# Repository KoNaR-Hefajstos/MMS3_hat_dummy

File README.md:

# MMS3 hat Dummy

## Sekcja 1: Dokumentacja Hat'a

### Krótki opis projektu
Hat Dummy to dystans mechaniczny. Tylko tyle

### Zgodność ze standardem ChainBus

* ❌ Używa złącza ChainBus, nie zmienia jego miejsca ani pinoutu. -> nie przesuwa addresów hat'a. Robi za głupi dystans mechaniczny
* ✅  Używa wyłącznie interfejsów I2C, SPI lub UART i nie inicjuje samodzielnie nowych transmisji (Nie jest master'em I2C albo SPI).
* ❌ Spełnia wymagania mechaniczne standardu (wymiary PCB, rozstaw otworów). -> Jest troche mniejszy
* ✅ Pobiera maksymalny prąd zgodny z ilością na jednego hat'a
* ✅ Obsługuje napięcie wejściowe BRD_VIN do wartości 48V.

### Komunikacja i adresowanie

Hat nie ma na sobie żadnych urządzeń

### Pinout złączy
Brak

### Konfiguracja układu (Zworki/Rezystory)
Brak

### Szczegółowy opis techniczny
Hat Dummy to dystans mechaniczny. Możesz go dać jeśli potrzebujesz mieć fizycznie więcej miejsca miedzy hat'ami. Nie zużywa adresu hat'a -> możesz go włożyć w dowolne miejsce między inne hat'y i elektrycznie ani programowo się nic nie zmieni

Bonusowo ma led'y które się świecą jak wybierzesz jakiegoś hat'a za nim. Elektrycznie nic nie zmienia

### Gotowe arkusze hierarchiczne
Brak

---

## Sekcja 2: Specyfikacja standardu ChainBus

### Architektura i łączenie modułów
Standard ChainBus umożliwia modułowe łączenie hatów. Na jednym MMS3 można zamontować pionowo **do 8 hat'ów**. Połączenie realizowane jest poprzez wpięcie złącza męskiego kolejnego hat'a w złącze żeńskie poprzedniego

### Komunikacja i sterowanie
Magistrala ChainBus jest w pełni cyfrowa. Płyta główna nie steruje bezpośrednio sygnałami ogólnego przeznaczenia (GPIO) na poszczególnych hat'ach. Wszelkie operacje (np. obsługa diod LED, odczyt krańcówek, generowanie sygnałów PWM) muszą być realizowane przez dedykowane układy scalone (np. ekspandery portów, sterowniki) komunikujące się przez interfejsy systemowe.

*Przykład:*
`MCU` $\rightarrow$ `Expander GPIO po I2C` $\rightarrow$ `Dioda LED`

Wybór aktywnego modułu realizowany jest przez układ przełącznika magistrali (bus switch) na płycie głównej. Dzięki temu linie I2C, SPI i UART są niezależne dla każdego hat'a (brak konfliktów adresów I2C między różnymi hatami).
* **Identyfikacja:** Każdy moduł powinien posiadać pamięć EEPROM na magistrali I2C w celu identyfikacji płyty przez system - układ M24C64-W skonfigurowany na adres `1010000` przy liniach adresowych A0, A1, A2 zwartych do masy.

### Zasilanie
Złącze ChainBus dostarcza następujące linie zasilania:

| Magistrala zasilania | Napięcie znamionowe | Maksymalny prąd (łączny dla 8 hatów) | Szacowany prąd na jeden hat |
| :------------------- | :-----------------: | :----------------------------------: | :-------------------------: |
| **5V**               |        5.0 V        |                1.0 A                 |           125 mA            |
| **12V stby**         |       12.0 V        |                0.5 A                 |            65 mA            |
| **BRD_VIN**          |   12.0 V – 48.0 V   |                1.5 A                 |           185 mA            |

*   Komponenty podłączone do linii `BRD_VIN` muszą być przystosowane do pracy z napięciem od 12V do **48 V**.
*   W przypadku zapotrzebowania na wyższą moc, dopuszczalne jest zastosowanie dodatkowego złącza zasilania XT60 (obciążalność do ok. 60 A).

### Wymagania mechaniczne i złącza
* **Wymiary PCB:** Niedozwolona jest zmiana obrysu płytki oraz położenia otworów montażowych, aby zachować kompatybilność mechaniczną.
* **Pozycjonowanie złączy ChainBus:** Położenie złącza standardu 2x16 SMD (raster 2.54 mm) musi być zgodne z szablonem. Złącze żeńskie montowane jest na stronie FRONT, natomiast złącze męskie na stronie BACK.
* **Interfejsy zewnętrzne:** Złącza wejścia/wyjścia (domyślnie standard JST-XH 2.5 mm o obciążalności do 3 A) oraz opcjonalne złącze XT60 powinny być umieszczone przy dolnej krawędzi płytki. Elementy regulacyjne i sygnalizacyjne (potencjometry, przełączniki, diody LED) należy lokalizować przy prawej krawędzi płytki.
* **Komponenty** Wszystkie komponenty powinny być na stronie front płytki żeby nie haczyły o elementy ze wcześniejszego hat'a

---

## Sekcja 3: Licencje

### Licencje projektu

*   **PCB:** CERN-OHL-P
*   **Software:** MIT License

[Template](https://github.com/KoNaR-Hefajstos/MMS3_hat_templates/) jest na licencji CC0 1.0 Universal. **Reszta projektu nie jest na tej licencji**

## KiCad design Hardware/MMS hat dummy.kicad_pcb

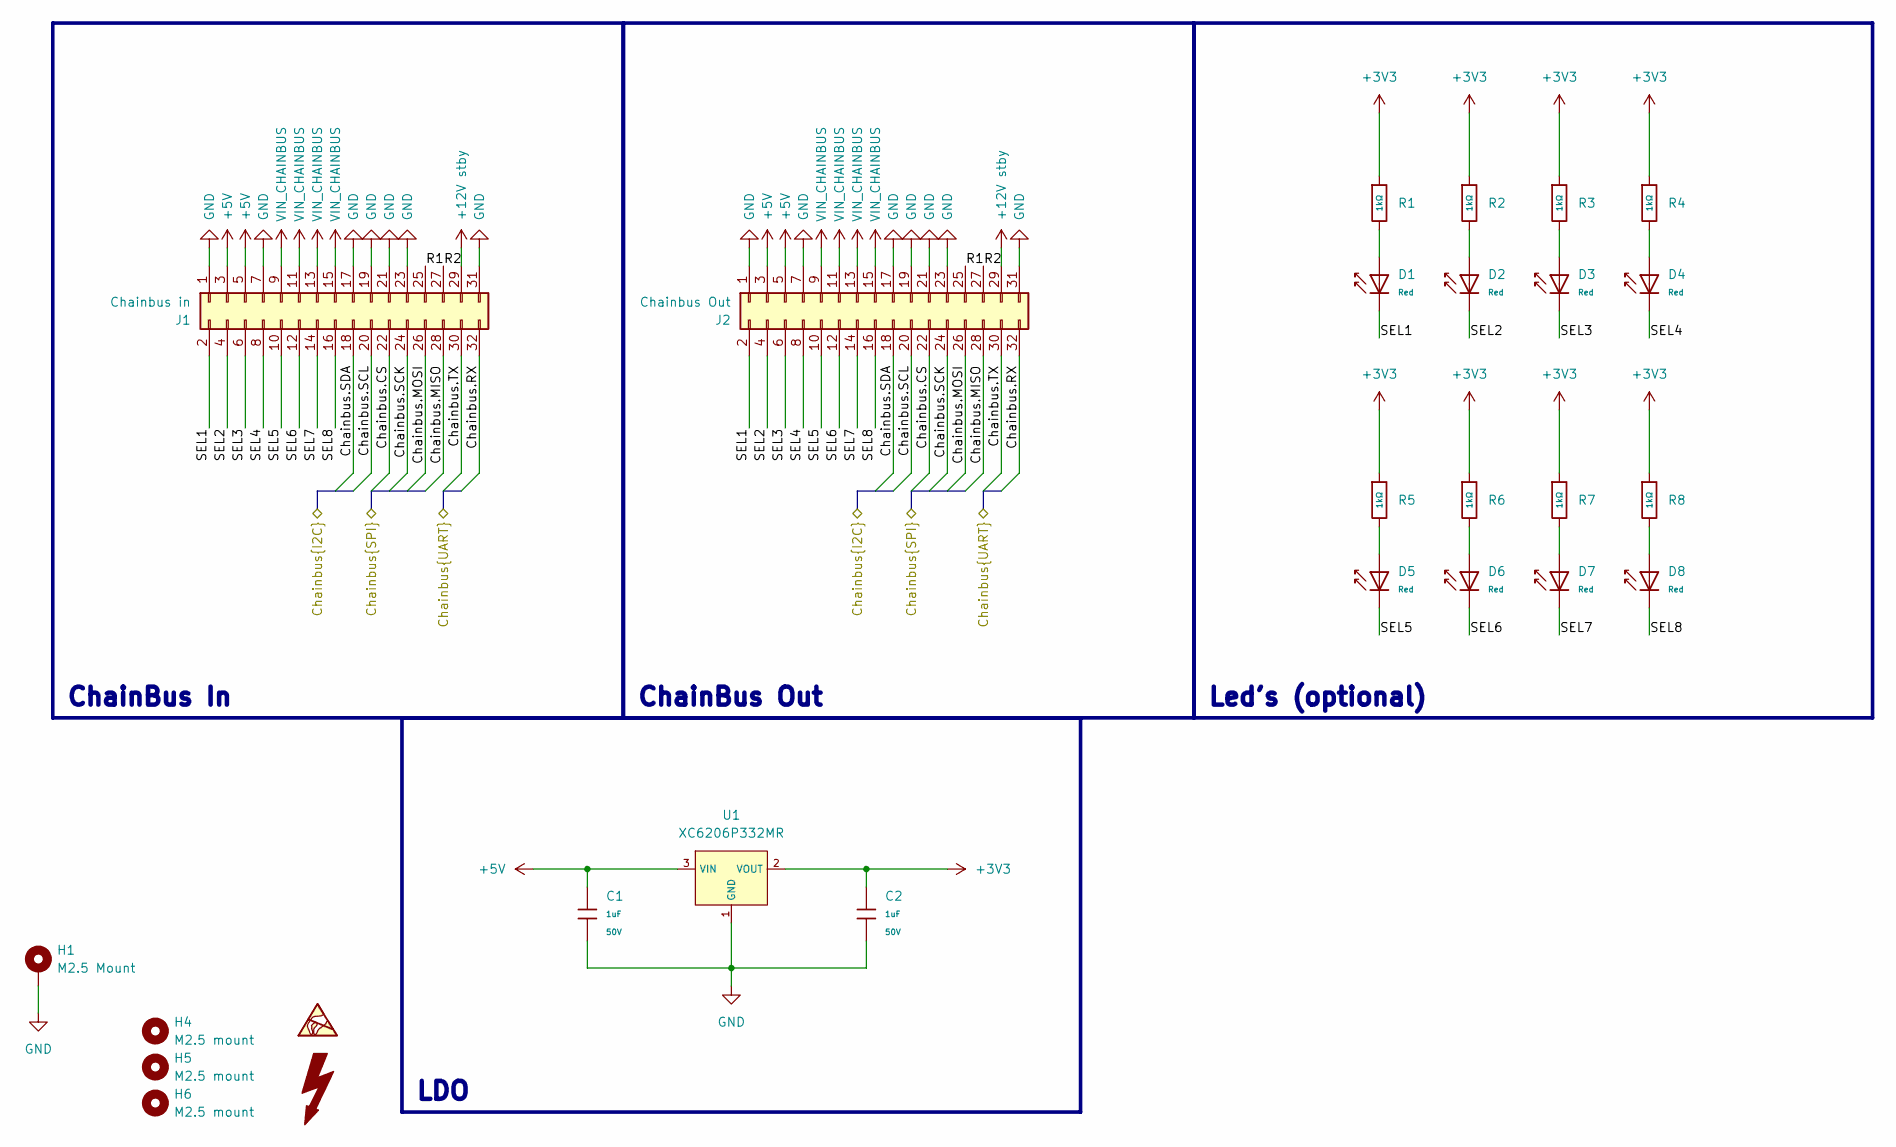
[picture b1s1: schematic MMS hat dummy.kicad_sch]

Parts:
C1, C2: 1uF; C_0603; Voltage Rated 50V; Tolerance ±10%; Part CL10A105KB8NNNC; LCSC C15849
D1, D2, D3, D4, D5, D6, D7, D8: Red; D_0603; Part KT-0603R; LCSC C2286
H1: M2.5 Mount; MountingHole_2.7mm_M2.5_DIN965_Pad_TopOnly
H4, H5, H6: M2.5 mount; MountingHole_2.7mm_M2.5
J1: Chainbus in; PinHeader_2x16_P2.54mm_Vertical_SMD
J2: Chainbus Out; PinSocket_2x16_P2.54mm_Vertical_SMD
R1, R2, R3, R4, R5, R6, R7, R8: 1kΩ; R_0603; Overload Voltage (Max) 75V; Tolerance ±1%; Part 0603WAF1001T5E; LCSC C21190
U1: XC6206P332MR; SOT-23-3_L2.9-W1.6-P1.90-LS2.8-BR; Output Voltage 3.3V; Dropout Voltage 680mV@(100mA); Part XC6206P332MR-G; LCSC C5446

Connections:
+3V3: C2.1, R1.1, R2.1, R3.1, R4.1, R5.1, R6.1, R7.1, R8.1, U1.2 (VOUT)
+5V: C1.1, J1.3, J1.5, J2.3, J2.5, U1.3 (VIN)
+12V stby: J1.29, J2.29
/Chainbus.CS: J1.22, J2.22
/Chainbus.MISO: J1.28, J2.28
/Chainbus.MOSI: J1.26, J2.26
/Chainbus.RX: J1.32, J2.32
/Chainbus.SCK: J1.24, J2.24
/Chainbus.SCL: J1.20, J2.20
/Chainbus.SDA: J1.18, J2.18
/Chainbus.TX: J1.30, J2.30
/R1: J1.25, J2.25
/R2: J1.27, J2.27
/SEL1: D1.1, J1.2, J2.2
/SEL2: D2.1, J1.4, J2.4
/SEL3: D3.1, J1.6, J2.6
/SEL4: D4.1, J1.8, J2.8
/SEL5: D5.1, J1.10, J2.10
/SEL6: D6.1, J1.12, J2.12
/SEL7: D7.1, J1.14, J2.14
/SEL8: D8.1, J1.16, J2.16
GND: C1.2, C2.2, H1.1 (1_1), J1.1, J1.7, J1.17, J1.19, J1.21, J1.23, J1.31, J2.1, J2.7, J2.17, J2.19, J2.21, J2.23, J2.31, U1.1 (GND)
unnamed: D1.2, R1.2
unnamed: D2.2, R2.2
unnamed: D3.2, R3.2
unnamed: D4.2, R4.2
unnamed: D5.2, R5.2
unnamed: D6.2, R6.2
unnamed: D7.2, R7.2
unnamed: D8.2, R8.2
VIN_CHAINBUS: J1.9, J1.11, J1.13, J1.15, J2.9, J2.11, J2.13, J2.15

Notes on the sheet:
ChainBus In
Led's (optional)
ChainBus Out
LDO

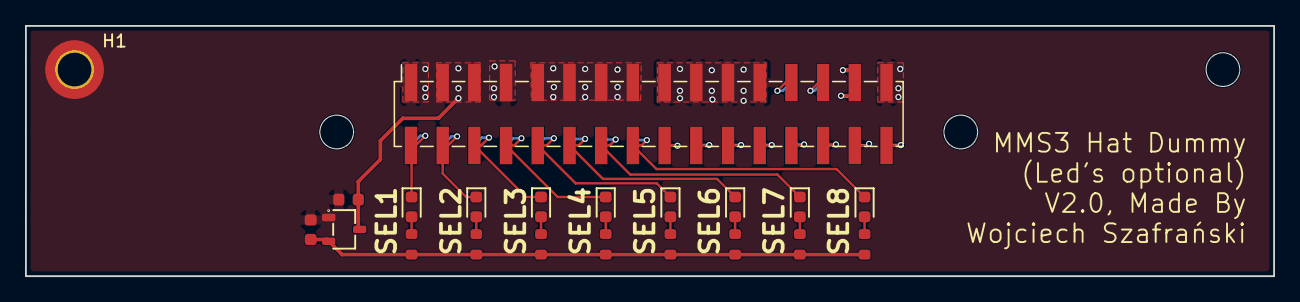
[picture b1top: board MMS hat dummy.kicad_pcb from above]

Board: 2 copper layers, 100.0 x 20.0 mm, 25 parts (1 on the bottom side), 31 nets.

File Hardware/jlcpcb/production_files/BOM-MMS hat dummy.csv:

Comment,Designator,Footprint,LCSC,Quantity
1kΩ,"R1,R2,R3,R4,R5,R6,R7,R8",R_0603,C21190,8
1uF,"C1,C2",C_0603,C15849,2
Red,"D1,D2,D3,D4,D5,D6,D7,D8",D_0603,C2286,8
XC6206P332MR,U1,SOT-23-3_L2.9-W1.6-P1.90-LS2.8-BR,C5446,1
Chainbus Out,J2,PinSocket_2x16_P2.54mm_Vertical_SMD,,1
Chainbus in,J1,PinHeader_2x16_P2.54mm_Vertical_SMD,,1
